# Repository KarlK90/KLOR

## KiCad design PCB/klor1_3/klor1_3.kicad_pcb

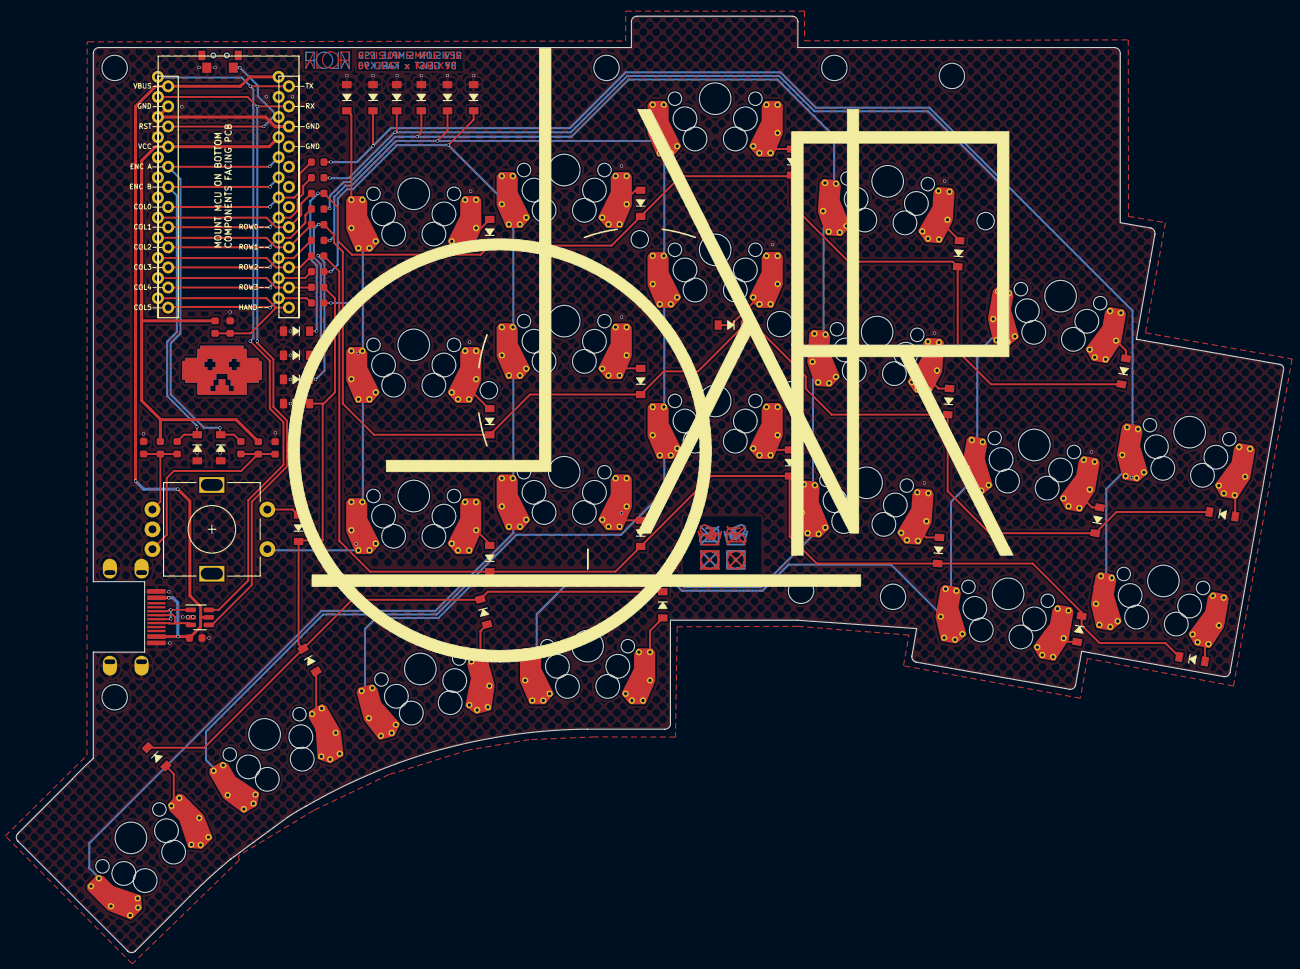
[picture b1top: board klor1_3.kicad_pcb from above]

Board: 2 copper layers, 160.0 x 118.2 mm, 89 parts (0 on the bottom side), 55 nets.

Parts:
C1, C2, C3: 100n; SMD-0603
D1, D2, D3, D4, D5, D6, D7, D8, D9, D10, D11, D12, D13, D14, D15, D16, D17, D18, D19, D20, D21, D22: D_Small; D_SOD-123
D23, D24, D25, D26, D27, D28, D29, D30, D31, D32, D33, D34: D_Zener; D_SOD-123
H1: TentingPuck; SplitkbTentingPuckWithoutCenterHole
J2: USB_C_Receptacle_USB2.0; USB_C_Receptacle_MUP_U22401
MH1, MH2, MH3, MH4, MH5, MH6, MH7, MH8: MountingHole_3.2mm_M3
MH9: MountingHole_2.2mm_M2
R1, R2, R3, R4, R5, R6, R7, R8, R9, R10, R11, R12, R13, R14, R15, R16: 10k; SMD-0603
RSW1: SW_Push; SMD_Tacticle_Switch_TS24CA_flipable
SW1, SW2, SW3, SW4, SW5, SW6, SW7, SW8, SW9, SW10, SW11, SW12, SW13, SW14, SW15, SW16, SW17, SW19, SW20, SW21, SW22: SW_PUSH-MX_W_LED; MX_KAILH_SOCKET_1U
SW18: ALPS EC11; RotaryEncoder_Alps_EC11E-Switch_Vertical_H20mm-keebio_modif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
U1: ProMicro
U2: USBLC6-2SC6; SOT-23-6

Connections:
ENCA: D33.1 (K), R1.2, U1.20 (F4/A3)
ENCB: D34.1 (K), R4.2, U1.19 (F5/A2)
ENC_B: D18.2 (A), SW18.S2
GND: C1.2, C2.2, C3.2, D23.2 (A), D24.2 (A), D25.2 (A), D26.2 (A), D27.2 (A), D28.2 (A), D29.2 (A), D30.2 (A), D31.2 (A), D32.2 (A), D33.2 (A), D34.2 (A), J2.A1 (GND), J2.A12 (GND), J2.B1 (GND), J2.B12 (GND), J2.S1 (SHIELD), R6.2, RSW1.1, SW18.C, U1.3 (GND), U1.4 (GND), U1.5 (2/D1/SDA), U1.6 (3/D0/SCL), U1.7 (4/D4), U1.23 (GND), U2.2 (GND)
unnamed: C1.1, R1.1, R2.2, SW18.B
unnamed: C2.1, R3.2, R4.1, SW18.A
unnamed: D1.2 (A), SW1.1
unnamed: D2.2 (A), SW2.1
unnamed: D3.2 (A), SW3.1
unnamed: D4.2 (A), SW4.1
unnamed: D5.2 (A), SW5.1
unnamed: D6.2 (A), SW6.1
unnamed: D7.2 (A), SW7.1
unnamed: D8.2 (A), SW8.1
unnamed: D9.2 (A), SW9.1
unnamed: D10.2 (A), SW10.1
unnamed: D11.2 (A), SW11.1
unnamed: D12.2 (A), SW12.1
unnamed: D13.2 (A), SW13.1
unnamed: D14.2 (A), SW14.1
unnamed: D15.2 (A), SW15.1
unnamed: D16.2 (A), SW16.1
unnamed: D17.2 (A), SW17.1
unnamed: D19.2 (A), SW19.1
unnamed: D20.2 (A), SW20.1
unnamed: D21.2 (A), SW21.1
unnamed: D22.2 (A), SW22.1
unnamed: R13.2, U1.8 (5/C6)
unnamed: R14.2, U1.9 (6/D7)
unnamed: R15.2, U1.10 (7/E6)
unnamed: R16.2, U1.11 (8/B4)
unnamed: R9.1, U1.16 (B1/15)
unnamed: R11.1, U1.14 (B2/16)
unnamed: R10.1, U1.15 (B3/14)
unnamed: R12.1, U1.13 (B6/10)
unnamed: R7.1, U1.18 (F6/A1)
unnamed: R8.1, U1.17 (F7/A0)
RESET: RSW1.2, U1.22 (RST)
RX: J2.A6 (D+), J2.B6 (D+), U2.3 (I/O2)
RX_ESD: U1.2 (RX1/D2), U2.4 (I/O2)
TX: J2.A7 (D-), J2.B7 (D-), U2.1 (I/O1)
TX_ESD: U1.1 (TX0/D3), U2.6 (I/O1)
VBUS: C3.1, J2.A4 (VBUS), J2.A9 (VBUS), J2.B4 (VBUS), J2.B9 (VBUS), U1.24 (RAW), U2.5 (VBUS)
VCC: R2.1, R3.1, R5.1, U1.21 (VCC)
col0: D23.1 (K), R7.2, SW11.2, SW17.2
col1: D24.1 (K), R8.2, SW5.2, SW10.2, SW16.2, SW22.2
col2: D25.1 (K), R9.2, SW4.2, SW9.2, SW15.2, SW21.2
col3: D26.1 (K), R10.2, SW3.2, SW8.2, SW14.2, SW20.2
col4: D27.1 (K), R11.2, SW2.2, SW7.2, SW13.2, SW19.2
col5: D28.1 (K), R12.2, SW1.2, SW6.2, SW12.2, SW18.S1
handness: R5.2, R6.1, U1.12 (9/B5)
row0: D1.1 (K), D2.1 (K), D3.1 (K), D4.1 (K), D5.1 (K), D29.1 (K), R13.1
row1: D6.1 (K), D7.1 (K), D8.1 (K), D9.1 (K), D10.1 (K), D11.1 (K), D30.1 (K), R14.1
row2: D12.1 (K), D13.1 (K), D14.1 (K), D15.1 (K), D16.1 (K), D17.1 (K), D31.1 (K), R15.1
row3: D18.1 (K), D19.1 (K), D20.1 (K), D21.1 (K), D22.1 (K), D32.1 (K), R16.1

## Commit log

2023-09-30 WIP: simple version
